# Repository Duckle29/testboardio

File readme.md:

# Testboardio

This repository holds a small example keyboard, made for the purpose of the "add new keyboard" guide in QMK

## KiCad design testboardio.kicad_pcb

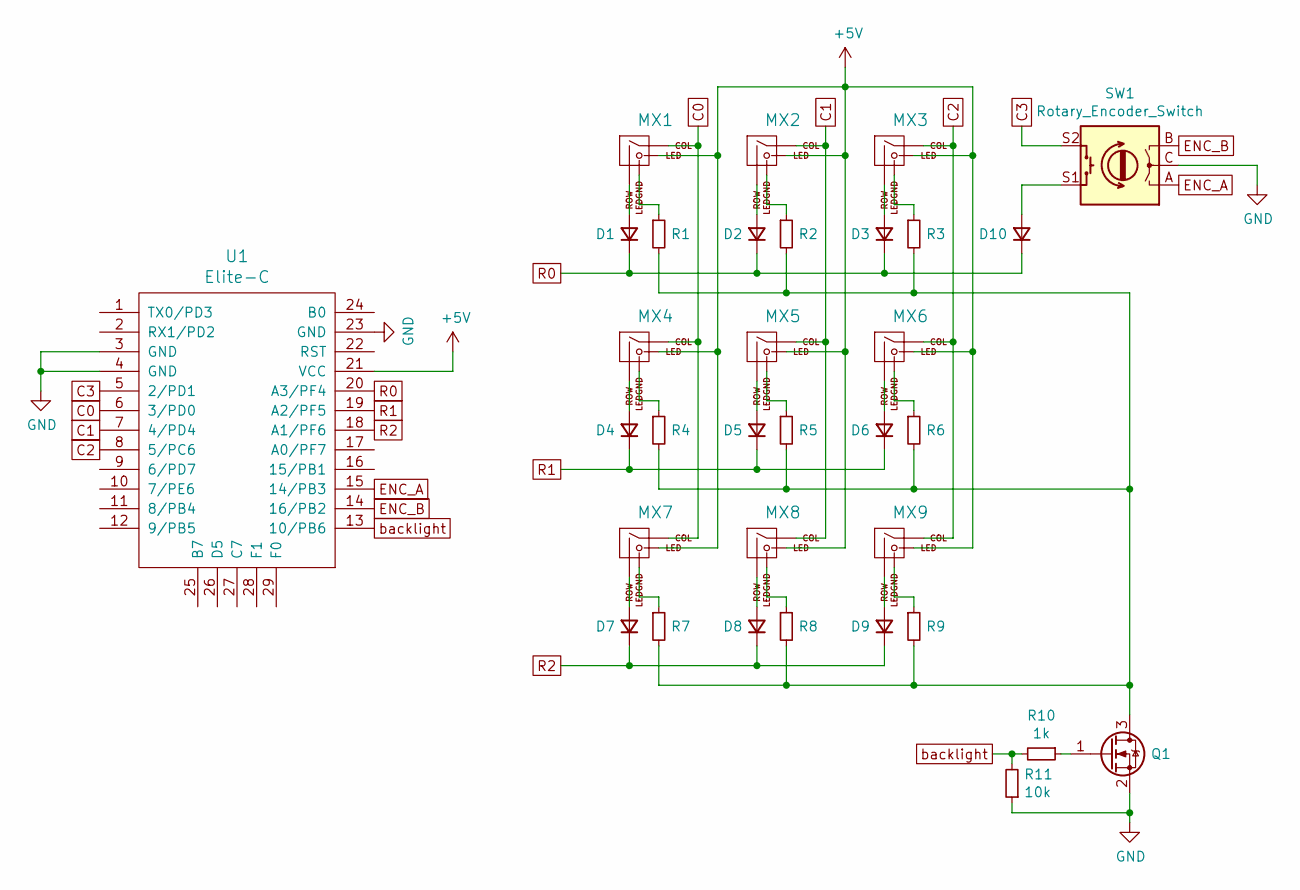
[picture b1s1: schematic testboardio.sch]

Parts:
D1, D2, D3, D4, D5, D6, D7, D8, D9, D10: D_Small; D_SMA_Handsoldering
MX1, MX2, MX3, MX4, MX5, MX6, MX7, MX8: MX-LED; MXOnly-1U
MX9: MX-LED; MXOnly-6U-Centered
Q1: Q_NMOS_GSD; SOT-23_Handsoldering
R1, R2, R3, R4, R5, R6, R7, R8, R9: R_Small; R_0603_1608Metric_Pad1.05x0.95mm_HandSolder
R10: 1k; R_0603_1608Metric_Pad1.05x0.95mm_HandSolder
R11: 10k; R_0603_1608Metric_Pad1.05x0.95mm_HandSolder
SW1: Rotary_Encoder_Switch; RotaryEncoder_Alps_EC11E-Switch_Vertical_H20mm
U1: Elite-C; Elite-C-ZigZag

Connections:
+5V: MX1.3 (LED), MX2.3 (LED), MX3.3 (LED), MX4.3 (LED), MX5.3 (LED), MX6.3 (LED), MX7.3 (LED), MX8.3 (LED), MX9.3 (LED), U1.21 (VCC)
C0: MX1.1 (COL), MX4.1 (COL), MX7.1 (COL), U1.6 (3/PD0)
C1: MX2.1 (COL), MX5.1 (COL), MX8.1 (COL), U1.7 (4/PD4)
C2: MX3.1 (COL), MX6.1 (COL), MX9.1 (COL), U1.8 (5/PC6)
C3: SW1.S2, U1.5 (2/PD1)
ENC_A: SW1.A, U1.15 (14/PB3)
ENC_B: SW1.B, U1.14 (16/PB2)
GND: Q1.2 (S), R11.1, SW1.C, U1.3 (GND), U1.4 (GND), U1.23 (GND)
unnamed: D1.2 (A), MX1.2 (ROW)
unnamed: D2.2 (A), MX2.2 (ROW)
unnamed: D3.2 (A), MX3.2 (ROW)
unnamed: D4.2 (A), MX4.2 (ROW)
unnamed: D5.2 (A), MX5.2 (ROW)
unnamed: D6.2 (A), MX6.2 (ROW)
unnamed: D7.2 (A), MX7.2 (ROW)
unnamed: D8.2 (A), MX8.2 (ROW)
unnamed: D9.2 (A), MX9.2 (ROW)
unnamed: D10.2 (A), SW1.S1
unnamed: MX1.4 (LEDGND), R1.1
unnamed: MX2.4 (LEDGND), R2.1
unnamed: MX3.4 (LEDGND), R3.1
unnamed: MX4.4 (LEDGND), R4.1
unnamed: MX5.4 (LEDGND), R5.1
unnamed: MX6.4 (LEDGND), R6.1
unnamed: MX7.4 (LEDGND), R7.1
unnamed: MX8.4 (LEDGND), R8.1
unnamed: MX9.4 (LEDGND), R9.1
unnamed: Q1.1 (G), R10.1
unnamed: Q1.3 (D), R1.2, R2.2, R3.2, R4.2, R5.2, R6.2, R7.2, R8.2, R9.2
R0: D1.1 (K), D2.1 (K), D3.1 (K), D10.1 (K), U1.20 (A3/PF4)
R1: D4.1 (K), D5.1 (K), D6.1 (K), U1.19 (A2/PF5)
R2: D7.1 (K), D8.1 (K), D9.1 (K), U1.18 (A1/PF6)
backlight: R10.2, R11.2, U1.13 (10/PB6)

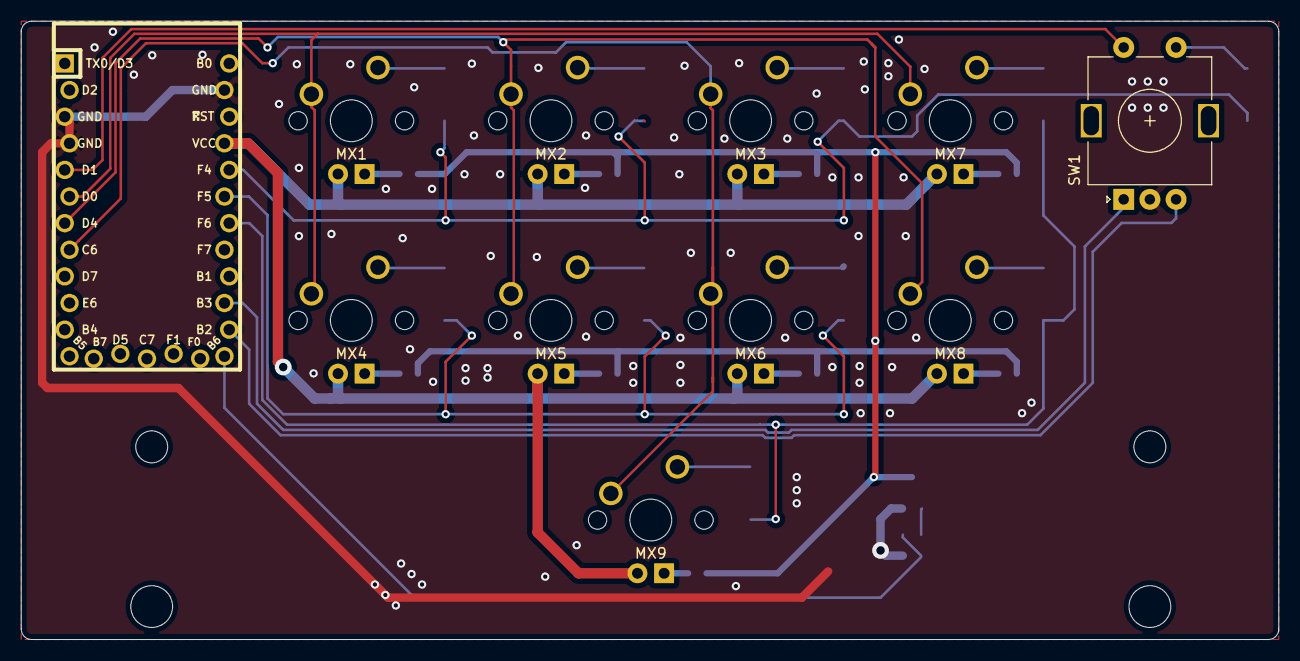
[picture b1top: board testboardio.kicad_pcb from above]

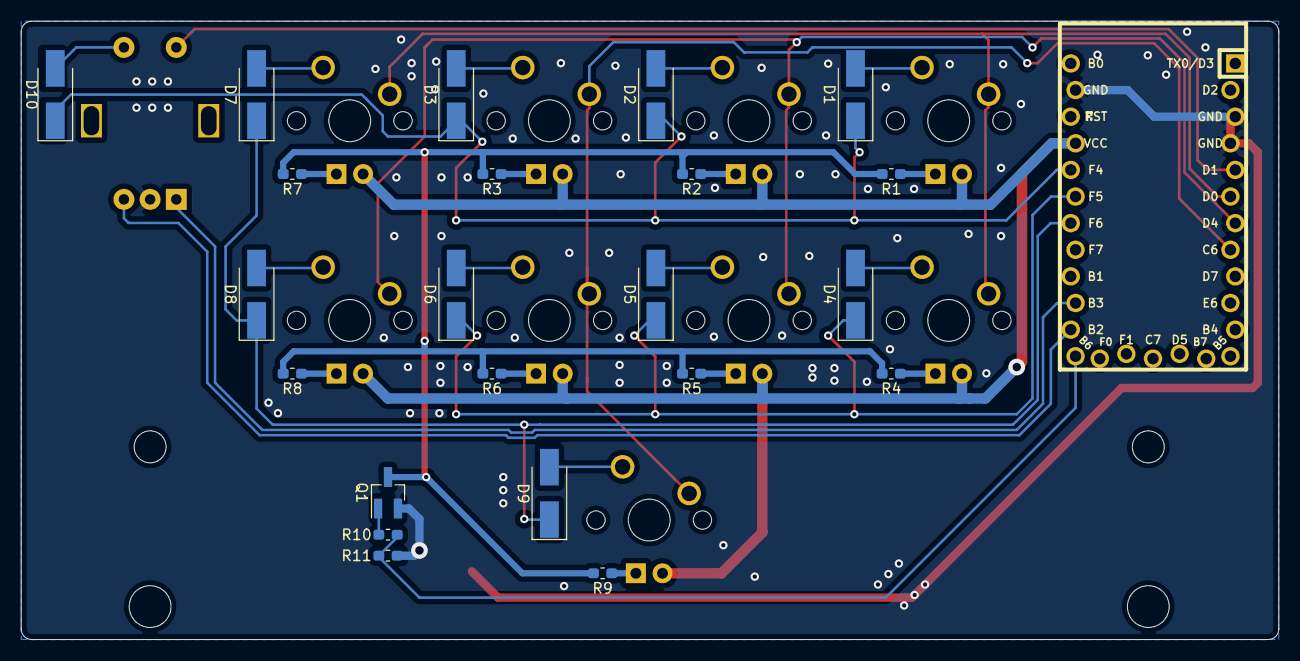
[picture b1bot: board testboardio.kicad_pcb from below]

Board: 2 copper layers, 120.0 x 59.0 mm, 33 parts (22 on the bottom side), 33 nets.

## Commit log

2020-08-27 Initial commit for example keyboard testboardio
2020-08-27 ignore more garbage
2020-08-27 Update LICENSE
2020-08-27 Added schematic
2020-08-27 Moved D10
